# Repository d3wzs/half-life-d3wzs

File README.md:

# Weather Sensor

This is a project that I made for Hack Clubs Half Life. It is a relatively compact weather sensor that can detect outside weather from inside. The code is far from complete but I find coding much easier when I can troubleshoot and test it with what im coding, so I'll finish it once its been built.

# Features/Attributes

- Indoor Temp Sensing - DHT22
- Outdoor Temp Sensing - DS18B20
- 2.8" TFT Display
- Interaction - Low Profile Switches
- Light Sensing - SAMIROB VEML7700 Ambient Light Sensor
- Custom PCB
- Custom Case

# Hardware

 - ESP32 CP2102 30 Pin Type C: Processing
 - SAMIROB VEML7700 Ambient Light Sensor: Light Sensing
 - TFT Display 2.8": Display
 - DHT22: Temp and Humidity Sensing
 - DS18B20: Temp Sensing
 - 2x Kailh Low Profile Switch 1350 Chocolate: Interaction
 - Custom PCB: does this need explanation?
 - Custom Case
If you want more specifics refer to the BOM.

# Repository Guide

- Case Folder - 3D models for the case
- PCB-Files Folder — PCB Files
- BOM.csv — bill of materials
- JOURNAL.md — project journal
- README.md - you r there
- weatherSensor.ino - Project Code

# Bill of Materials 

| Item | Qty | Supplier | Cost/item | Total Cost | link |
|---|---|---|---|---|---|
| ESP32 CP2102 30 Pin Type C | 1 | Aliexpress | $4.39 | $4.39 | https://www.aliexpress.com/item/1005007059457759.html?spm=a2g0o.productlist.main.11.46a851a1EcOz6O&algo_pvid=48e96717-31fd-498e-90c1-19e31a880a44&algo_exp_id=48e96717-31fd-498e-90c1-19e31a880a44-10&pdp_ext_f=%7B%22order%22%3A%225412%22%2C%22spu_best_type%22%3A%22price%22%2C%22eval%22%3A%221%22%2C%22fromPage%22%3A%22search%22%7D&pdp_npi=6%40dis%21USD%212.97%212.96%21%21%2119.73%2119.66%21%402103129017931430541374212e1039%2112000039267548455%21sea%21CA%217748192322%21X%211%210%21n_tag%3A-29919%3Bd%3Aa40d61bf%3Bm03_new_user%3A-29895%3BpisId%3A5000000219084765&curPageLogUid=TuAuhaCvljNJ&utparam-url=scene%3Asearch%7Cquery_from%3A%7Cx_object_id%3A1005007059457759%7C_p_origin_prod%3A |
| SAMIROB VEML7700 Ambient Light Sensor | 1 | Aliexpress | $4.27 | $4.27 | https://www.aliexpress.com/item/1005009958037220.html?spm=a2g0o.productlist.main.2.75fb7681j6Ui7M&algo_pvid=dfa98390-67e2-4431-9eba-9c595f163622&algo_exp_id=dfa98390-67e2-4431-9eba-9c595f163622-1&pdp_ext_f=%7B%22order%22%3A%224310%22%2C%22spu_best_type%22%3A%22price%22%2C%22eval%22%3A%221%22%2C%22fromPage%22%3A%22search%22%7D&pdp_npi=6%40dis%21USD%218.55%214.27%21%21%2156.75%2128.37%21%402103128817930590690892222e0f66%2112000050688182705%21sea%21CA%217748192322%21X%211%210%21n_tag%3A-29919%3Bd%3Aa40d61bf%3Bm03_new_user%3A-29895&curPageLogUid=fbrqLCyzBraY&utparam-url=scene%3Asearch%7Cquery_from%3A%7Cx_object_id%3A1005009958037220%7C_p_origin_prod%3A |
| TFT Display 2.8" | 1 | Aliexpress | $6.28 | $6.28 | https://www.aliexpress.com/item/1005009761383945.html?spm=a2g0o.productlist.main.15.2387633cAe8Gow&algo_pvid=7d59ccbc-6402-42eb-9cfb-cf0d796d9aca&algo_exp_id=7d59ccbc-6402-42eb-9cfb-cf0d796d9aca-14&pdp_ext_f=%7B%22order%22%3A%225189%22%2C%22spu_best_type%22%3A%22price%22%2C%22eval%22%3A%221%22%2C%22fromPage%22%3A%22search%22%7D&pdp_npi=6%40dis%21USD%215.50%215.49%21%21%2136.50%2136.43%21%402101e80b17930597168566119e0db4%2112000050079449343%21sea%21CA%217748192322%21X%211%210%21n_tag%3A-29919%3Bd%3Aa40d61bf%3Bm03_new_user%3A-29895%3BpisId%3A5000000219084765&curPageLogUid=fUFAvJOdPnyL&utparam-url=scene%3Asearch%7Cquery_from%3A%7Cx_object_id%3A1005009761383945%7C_p_origin_prod%3A |
| DHT22 | 1 | Aliexpress | $1.49 | $1.49 | https://www.aliexpress.com/item/1005010283810231.html?spm=a2g0o.productlist.main.9.1eaa9de5jsxKli&algo_pvid=a384db54-b4ae-4c8e-b987-75d3980b8181&algo_exp_id=a384db54-b4ae-4c8e-b987-75d3980b8181-8&pdp_ext_f=%7B%22order%22%3A%221046%22%2C%22spu_best_type%22%3A%22price%22%2C%22eval%22%3A%221%22%2C%22fromPage%22%3A%22search%22%7D&pdp_npi=6%40dis%21USD%212.16%211.49%21%21%2114.34%219.94%21%402101f43b17931139321376665e0f3c%2112000051781867490%21sea%21CA%217748192322%21X%211%210%21n_tag%3A-29919%3Bd%3Aa40d61bf%3Bm03_new_user%3A-29895&curPageLogUid=BakEn6D2S6Zy&utparam-url=scene%3Asearch%7Cquery_from%3A%7Cx_object_id%3A1005010283810231%7C_p_origin_prod%3A |
| DS18B20 | 1 | Aliexpress | $2.90 | $2.90 | https://www.aliexpress.com/item/1005011548245287.html?spm=a2g0o.productlist.main.3.2bf042419AMdu4&algo_pvid=5bb63854-c1d3-4825-9098-616771c78253&algo_exp_id=5bb63854-c1d3-4825-9098-616771c78253-2&pdp_ext_f=%7B%22order%22%3A%221742%22%2C%22eval%22%3A%221%22%2C%22fromPage%22%3A%22search%22%7D&pdp_npi=6%40dis%21USD%212.91%212.90%21%21%2119.33%2119.26%21%402103128817931140735761711e0dd5%2112000055887000991%21sea%21CA%217748192322%21X%211%210%21n_tag%3A-29919%3Bd%3Aa40d61bf%3Bm03_new_user%3A-29895%3BpisId%3A5000000219084765&curPageLogUid=y8eNtvqtPUGa&utparam-url=scene%3Asearch%7Cquery_from%3A%7Cx_object_id%3A1005011548245287%7C_p_origin_prod%3A |
| Low Profile Switches | 1 | Aliexpress | $3.82 | $3.82 | https://www.aliexpress.com/item/1005005979847053.html?spm=a2g0o.productlist.main.2.4ad74897oZOMR5&algo_pvid=2c296add-5454-4b3c-a762-977344eb3b0e&algo_exp_id=2c296add-5454-4b3c-a762-977344eb3b0e-1&pdp_ext_f=%7B%22order%22%3A%2281%22%2C%22eval%22%3A%221%22%2C%22fromPage%22%3A%22search%22%7D&pdp_npi=6%40dis%21USD%213.82%213.82%21%21%213.82%213.82%21%402101c4b817931572409778871e0d2e%2112000035151278587%21sea%21CA%217748192322%21X%211%210%21n_tag%3A-29919%3Bd%3Aa40d61bf%3Bm03_new_user%3A-29895&curPageLogUid=kl5wdgyCi0Wz&utparam-url=scene%3Asearch%7Cquery_from%3A%7Cx_object_id%3A1005005979847053%7C_p_origin_prod%3A |
| PCB | 1 | JLCPCB | $5.50 | $5.50 | https://cart.jlcpcb.com/quote?spm=jlcpcb.Public.2006 |
| Estimated total shipping | 1 |   |   | $0.00 |   |

# Media

sorry for the formating, im not sure how to fix it

# Author

- d3wzs(d3wzy)

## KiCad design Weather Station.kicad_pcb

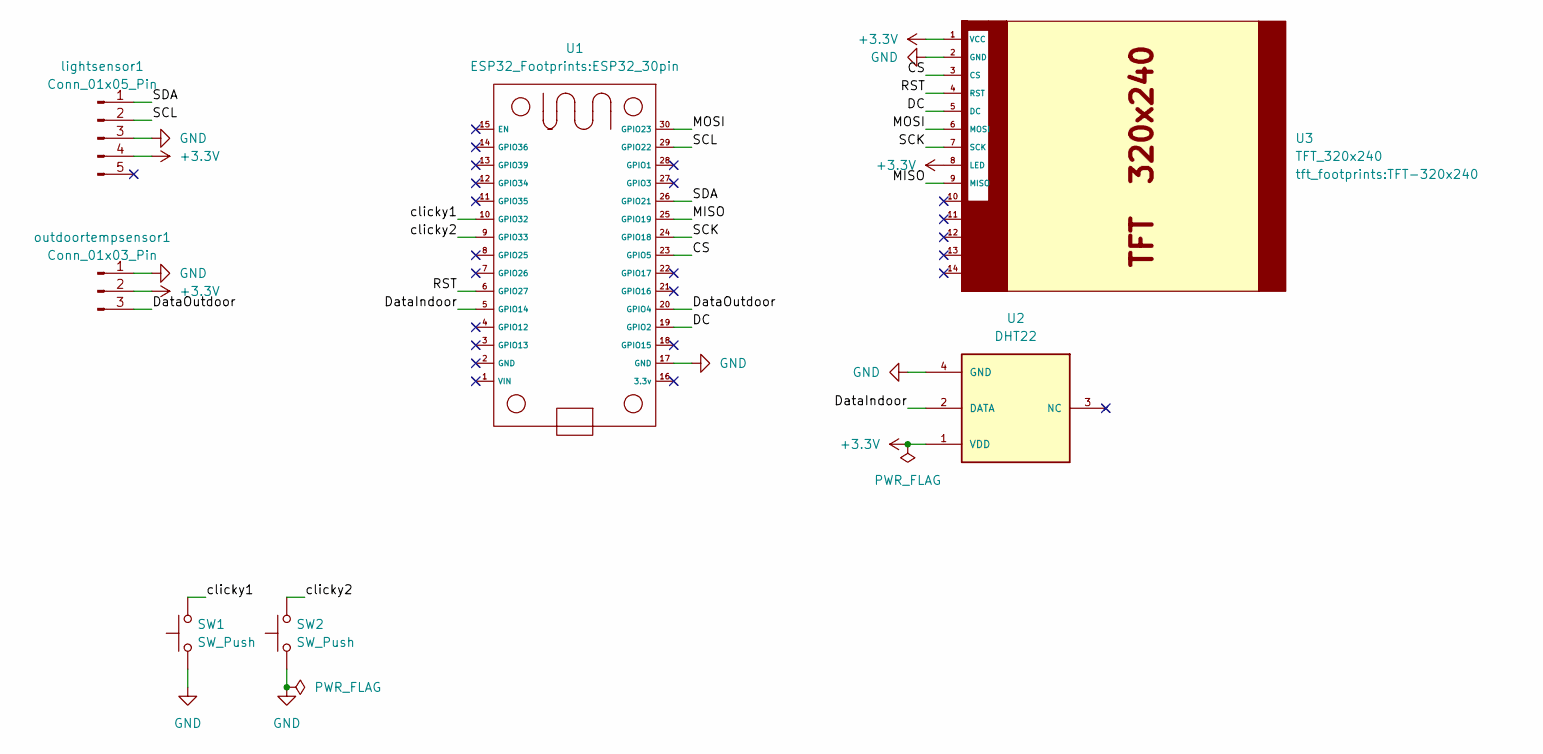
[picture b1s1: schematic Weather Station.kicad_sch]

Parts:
SW1, SW2: SW_Push; Kailh Choc Low-Profile Switches
U1: ESP32_30pin
U2: DHT22; XDCR_DHT22
U3: TFT_320x240; TFT-320x240
lightsensor1: Conn_01x05_Pin; PinHeader_1x05_P2.54mm_Vertical
outdoortempsensor1: Conn_01x03_Pin; FanPinHeader_1x03_P2.54mm_Vertical

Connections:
+3.3V: U2.1 (VDD), U3.1 (VCC), U3.8 (LED), lightsensor1.4, outdoortempsensor1.2
/CS: U1.23 (GPIO5), U3.3 (CS)
/DC: U1.19 (GPIO2), U3.5 (DC)
/DataIndoor: U1.5 (GPIO14), U2.2 (DATA)
/DataOutdoor: U1.20 (GPIO4), outdoortempsensor1.3
/MISO: U1.25 (GPIO19), U3.9 (MISO)
/MOSI: U1.30 (GPIO23), U3.6 (MOSI)
/RST: U1.6 (GPIO27), U3.4 (RST)
/SCK: U1.24 (GPIO18), U3.7 (SCK)
/SCL: U1.29 (GPIO22), lightsensor1.2
/SDA: U1.26 (GPIO21), lightsensor1.1
/clicky1: SW1.2, U1.10 (GPIO32)
/clicky2: SW2.2, U1.9 (GPIO33)
GND: SW1.1, SW2.1, U1.17 (GND), U2.4 (GND), U3.2 (GND), lightsensor1.3, outdoortempsensor1.1

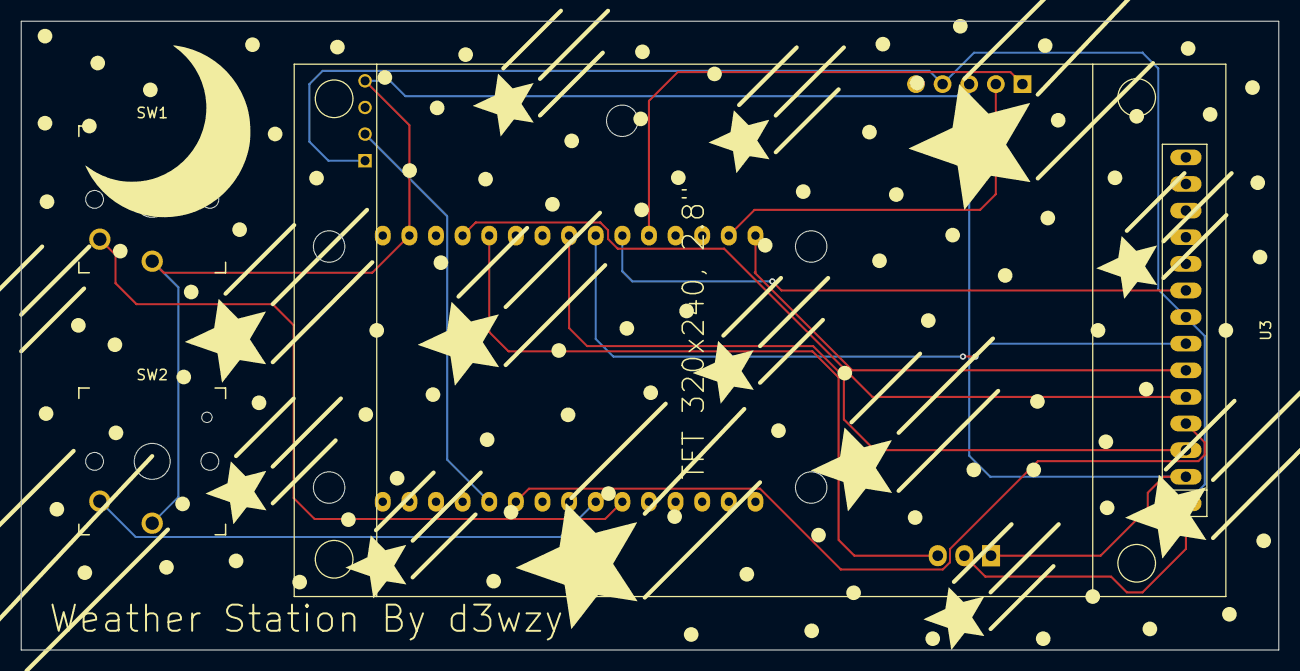
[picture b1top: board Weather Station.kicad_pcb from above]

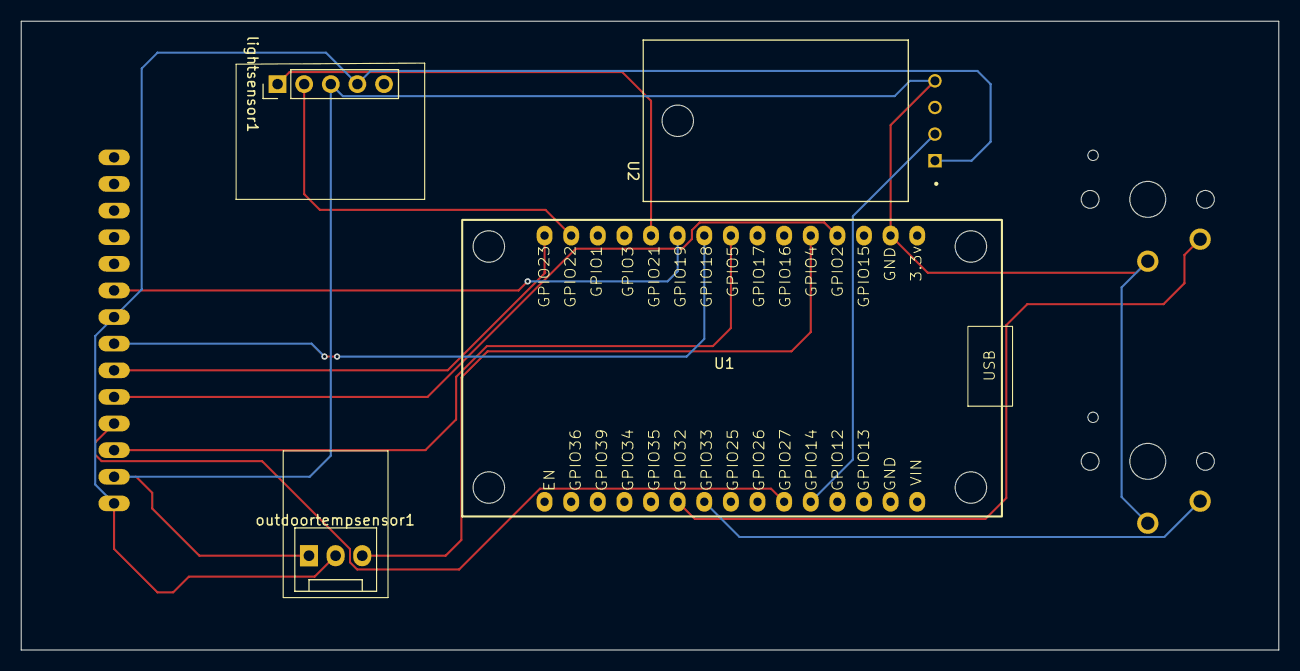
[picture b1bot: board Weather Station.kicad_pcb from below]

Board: 2 copper layers, 120.0 x 60.0 mm, 7 parts (4 on the bottom side), 14 nets.
